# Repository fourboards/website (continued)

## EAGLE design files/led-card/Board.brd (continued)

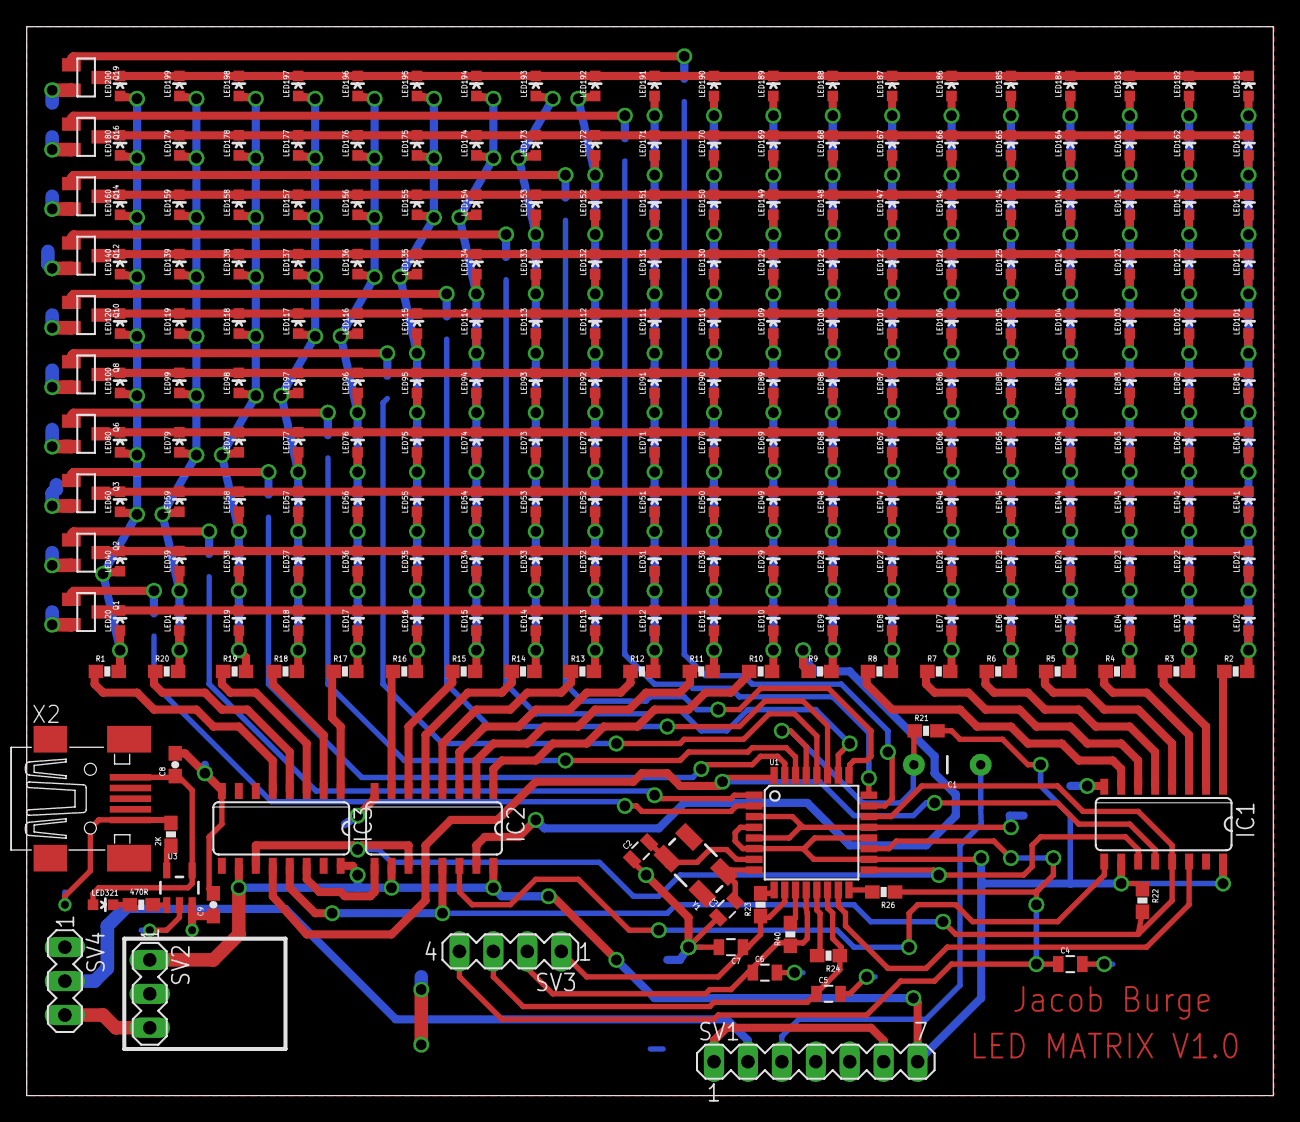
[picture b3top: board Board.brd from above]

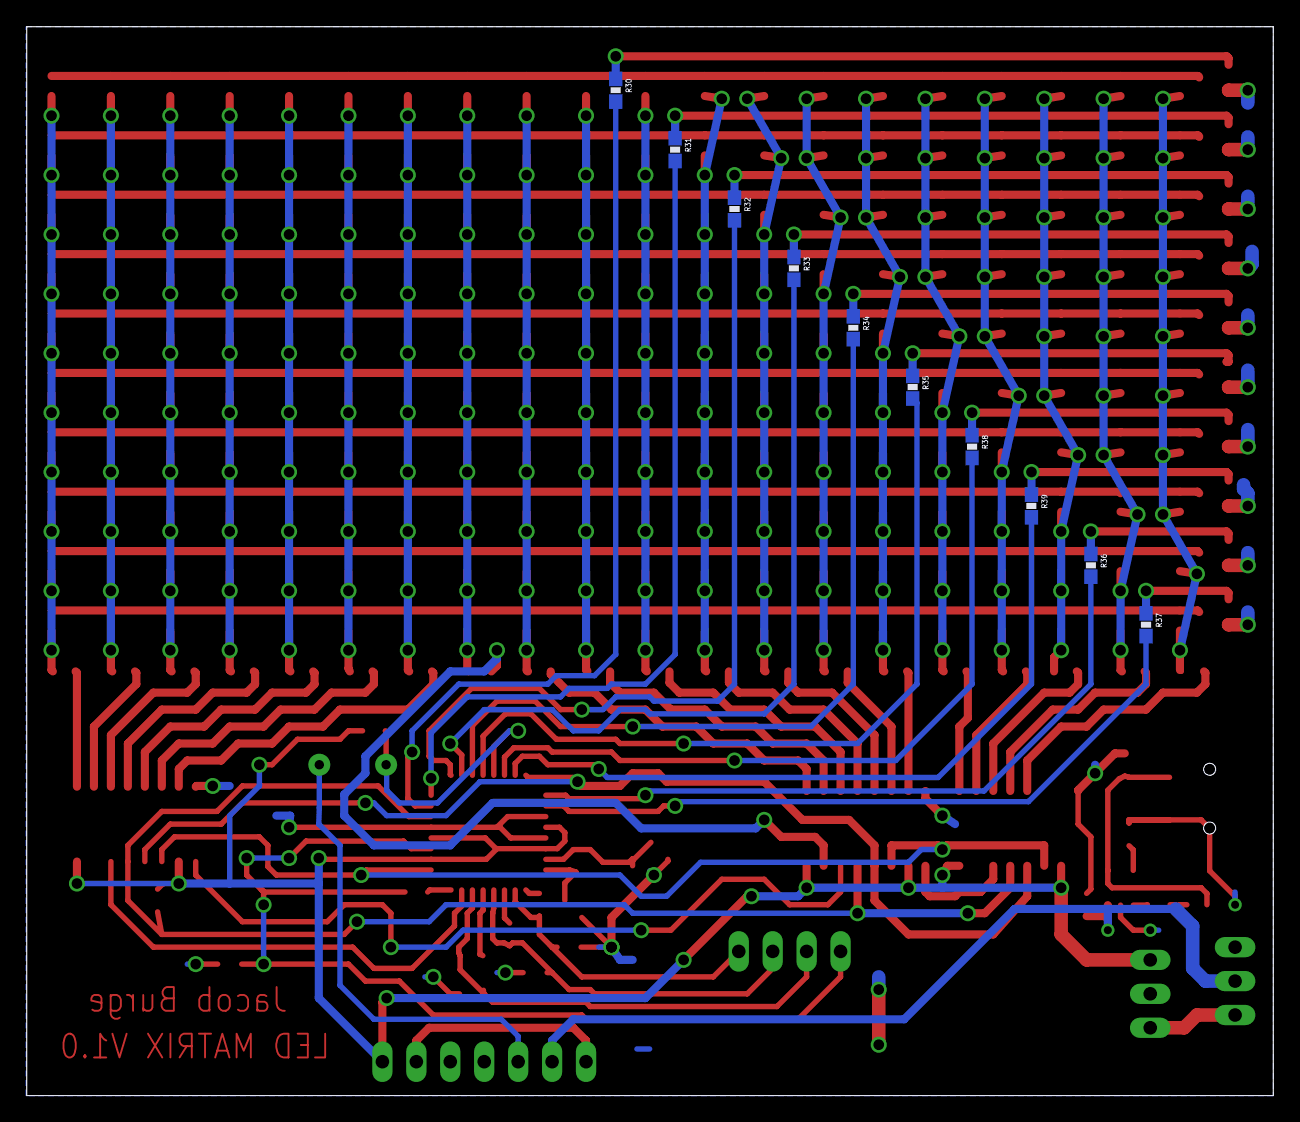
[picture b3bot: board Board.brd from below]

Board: 2 copper layers, 93.3 x 80.0 mm, 269 parts (10 on the bottom side), 96 nets.

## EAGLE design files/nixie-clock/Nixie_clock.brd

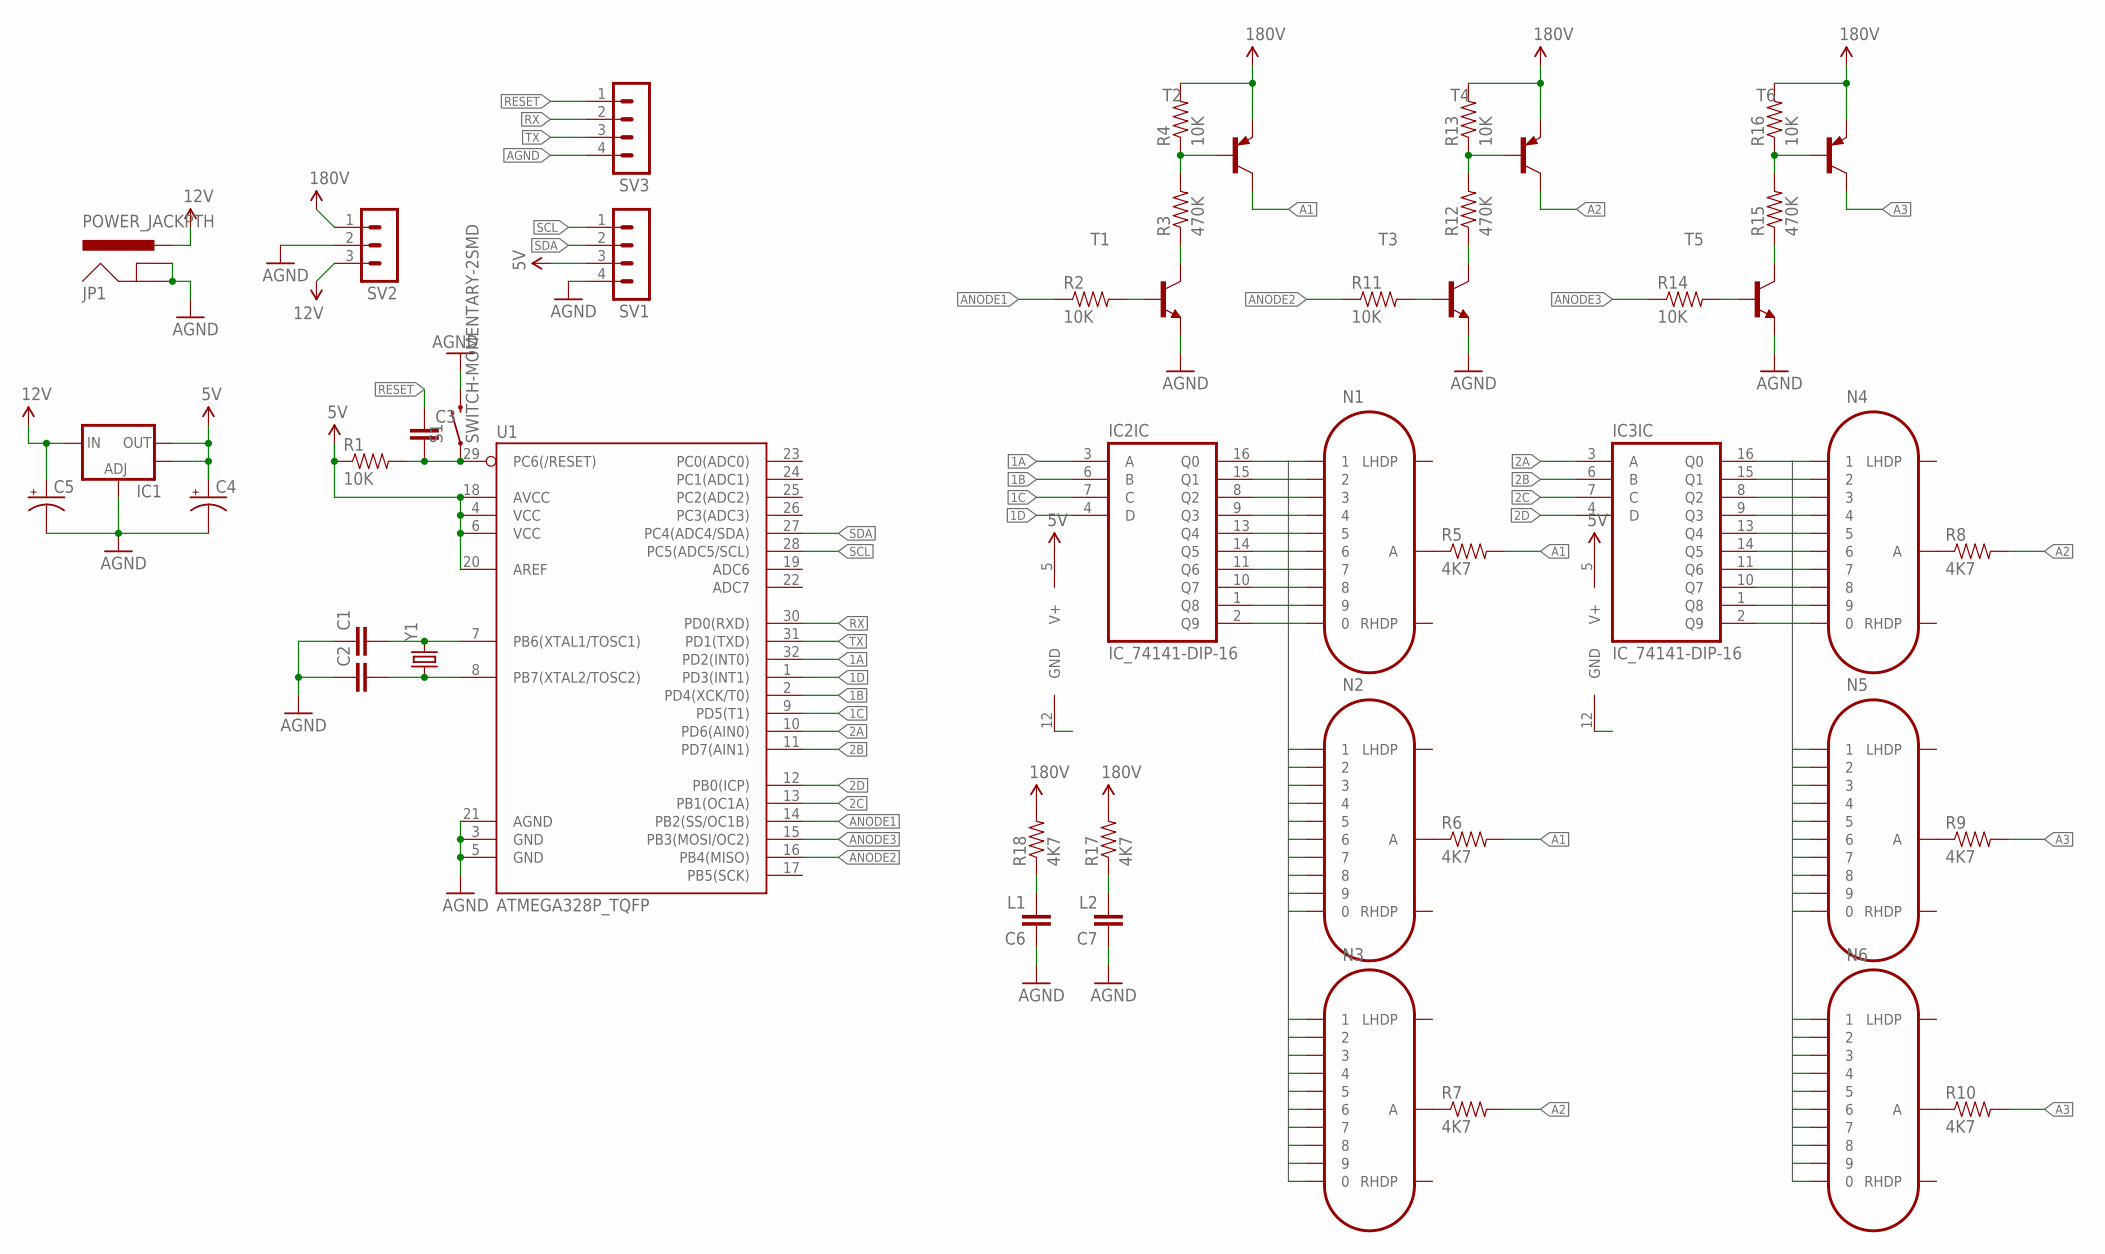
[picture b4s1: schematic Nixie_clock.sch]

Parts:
C1, C2, C3: CAPPTH; CAP-PTH-SMALL
C4, C5: 10UF-25V-20%(PTH); CPOL-RADIAL-10UF-25V
C6: L1; CAP-PTH-SMALL
C7: L2; CAP-PTH-SMALL
IC1: V_REG_LM1117SOT223; SOT223
IC2, IC3: IC_74141-DIP-16; DIL16
JP1: POWER_JACKPTH; POWER_JACK_PTH
N1, N2, N3, N4, N5, N6: IN-14
R1, R2, R11, R14: 10K; 0603-RES
R3, R12, R15: 470K; AXIAL-0.3
R4, R13, R16: 10K; AXIAL-0.3
R5, R6, R7, R8, R9, R10, R17, R18: 4K7; AXIAL-0.3
S1: SWITCH-MOMENTARY-2SMD; TACTILE-SWITCH-SMD
SV1, SV3: MA04-1
SV2: MA03-1
T1, T3, T5: MPSA42-NPN-TO92-EBC; TO92-EBC
T2, T4, T6: MPSA92-PNP-TO92-EBC; TO92-EBC
U1: ATMEGA328P_TQFP; TQFP32-08
Y1: CRYSTALHC49US; HC49US

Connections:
1.0V: R4.P$2 (2), R13.P$2 (2), R16.P$2 (2), R17.P$2 (2), R18.P$2 (2), SV2.1, T2.E, T4.E, T6.E
1A: IC2.3 (A), U1.32 (PD2(INT0))
1B: IC2.6 (B), U1.2 (PD4(XCK/T0))
1C: IC2.7 (C), U1.9 (PD5(T1))
1D: IC2.4 (D), U1.1 (PD3(INT1))
2A: IC3.3 (A), U1.10 (PD6(AIN0))
2B: IC3.6 (B), U1.11 (PD7(AIN1))
2C: IC3.7 (C), U1.13 (PB1(OC1A))
2D: IC3.4 (D), U1.12 (PB0(ICP))
5V: C4.1 (+), IC1.2 (OUT), IC1.4 (OUT), IC2.5 (V+), IC3.5 (V+), R1.1, SV1.3, U1.4 (VCC), U1.6 (VCC), U1.18 (AVCC), U1.20 (AREF)
12V: C5.1 (+), IC1.3 (IN), JP1.PWR, SV2.3
A1: R5.P$2 (2), R6.P$2 (2), T2.C
A2: R7.P$2 (2), R8.P$2 (2), T4.C
A3: R9.P$2 (2), R10.P$2 (2), T6.C
AGND: C1.1, C2.1, C4.2 (-), C5.2 (-), C6.1, C7.1, IC1.1 (ADJ), IC2.12 (GND), IC3.12 (GND), JP1.GND, JP1.GNDBREAK, S1.3 (2), SV1.4, SV2.2, SV3.4, T1.E, T3.E, T5.E, U1.3 (GND), U1.5 (GND), U1.21 (AGND)
ANODE1: R2.1, U1.14 (PB2(SS/OC1B))
ANODE2: R11.1, U1.16 (PB4(MISO))
ANODE3: R14.1, U1.15 (PB3(MOSI/OC2))
unnamed: C1.2, U1.7 (PB6(XTAL1/TOSC1)), Y1.2
unnamed: C2.2, U1.8 (PB7(XTAL2/TOSC2)), Y1.1
unnamed: C3.2, R1.2, S1.1, U1.29 (PC6(/RESET))
unnamed: R2.2, T1.B
unnamed: R3.P$1 (1), T1.C
unnamed: R3.P$2 (2), R4.P$1 (1), T2.B
unnamed: N1.A, R5.P$1 (1)
unnamed: N2.A, R6.P$1 (1)
unnamed: N3.A, R7.P$1 (1)
unnamed: N4.A, R8.P$1 (1)
unnamed: N5.A, R9.P$1 (1)
unnamed: N6.A, R10.P$1 (1)
unnamed: R11.2, T3.B
unnamed: R12.P$1 (1), T3.C
unnamed: R12.P$2 (2), R13.P$1 (1), T4.B
unnamed: R14.2, T5.B
unnamed: R15.P$1 (1), T5.C
unnamed: R15.P$2 (2), R16.P$1 (1), T6.B
unnamed: C6.2, R18.P$1 (1)
unnamed: C7.2, R17.P$1 (1)
NIXIE0: IC2.16 (Q0), N1.0, N2.0, N3.0
NIXIE1: IC2.15 (Q1), N1.1, N2.1, N3.1
NIXIE2: IC2.8 (Q2), N1.2, N2.2, N3.2
NIXIE3: IC2.9 (Q3), N1.3, N2.3, N3.3
NIXIE4: IC2.13 (Q4), N1.4, N2.4, N3.4
NIXIE5: IC2.14 (Q5), N1.5, N2.5, N3.5
NIXIE6: IC2.11 (Q6), N1.6, N2.6, N3.6
NIXIE7: IC2.10 (Q7), N1.7, N2.7, N3.7
NIXIE8: IC2.1 (Q8), N1.8, N2.8, N3.8
NIXIE9: IC2.2 (Q9), N1.9, N2.9, N3.9
NIXIEB0: IC3.16 (Q0), N4.0, N5.0, N6.0
NIXIEB1: IC3.15 (Q1), N4.1, N5.1, N6.1
NIXIEB2: IC3.8 (Q2), N4.2, N5.2, N6.2
NIXIEB3: IC3.9 (Q3), N4.3, N5.3, N6.3
NIXIEB4: IC3.13 (Q4), N4.4, N5.4, N6.4
NIXIEB5: IC3.14 (Q5), N4.5, N5.5, N6.5
NIXIEB6: IC3.11 (Q6), N4.6, N5.6, N6.6
NIXIEB7: IC3.10 (Q7), N4.7, N5.7, N6.7
NIXIEB8: IC3.1 (Q8), N4.8, N5.8, N6.8
NIXIEB9: IC3.2 (Q9), N4.9, N5.9, N6.9
RESET: C3.1, SV3.1
RX: SV3.2, U1.30 (PD0(RXD))
SCL: SV1.1, U1.28 (PC5(ADC5/SCL))
SDA: SV1.2, U1.27 (PC4(ADC4/SDA))
TX: SV3.3, U1.31 (PD1(TXD))

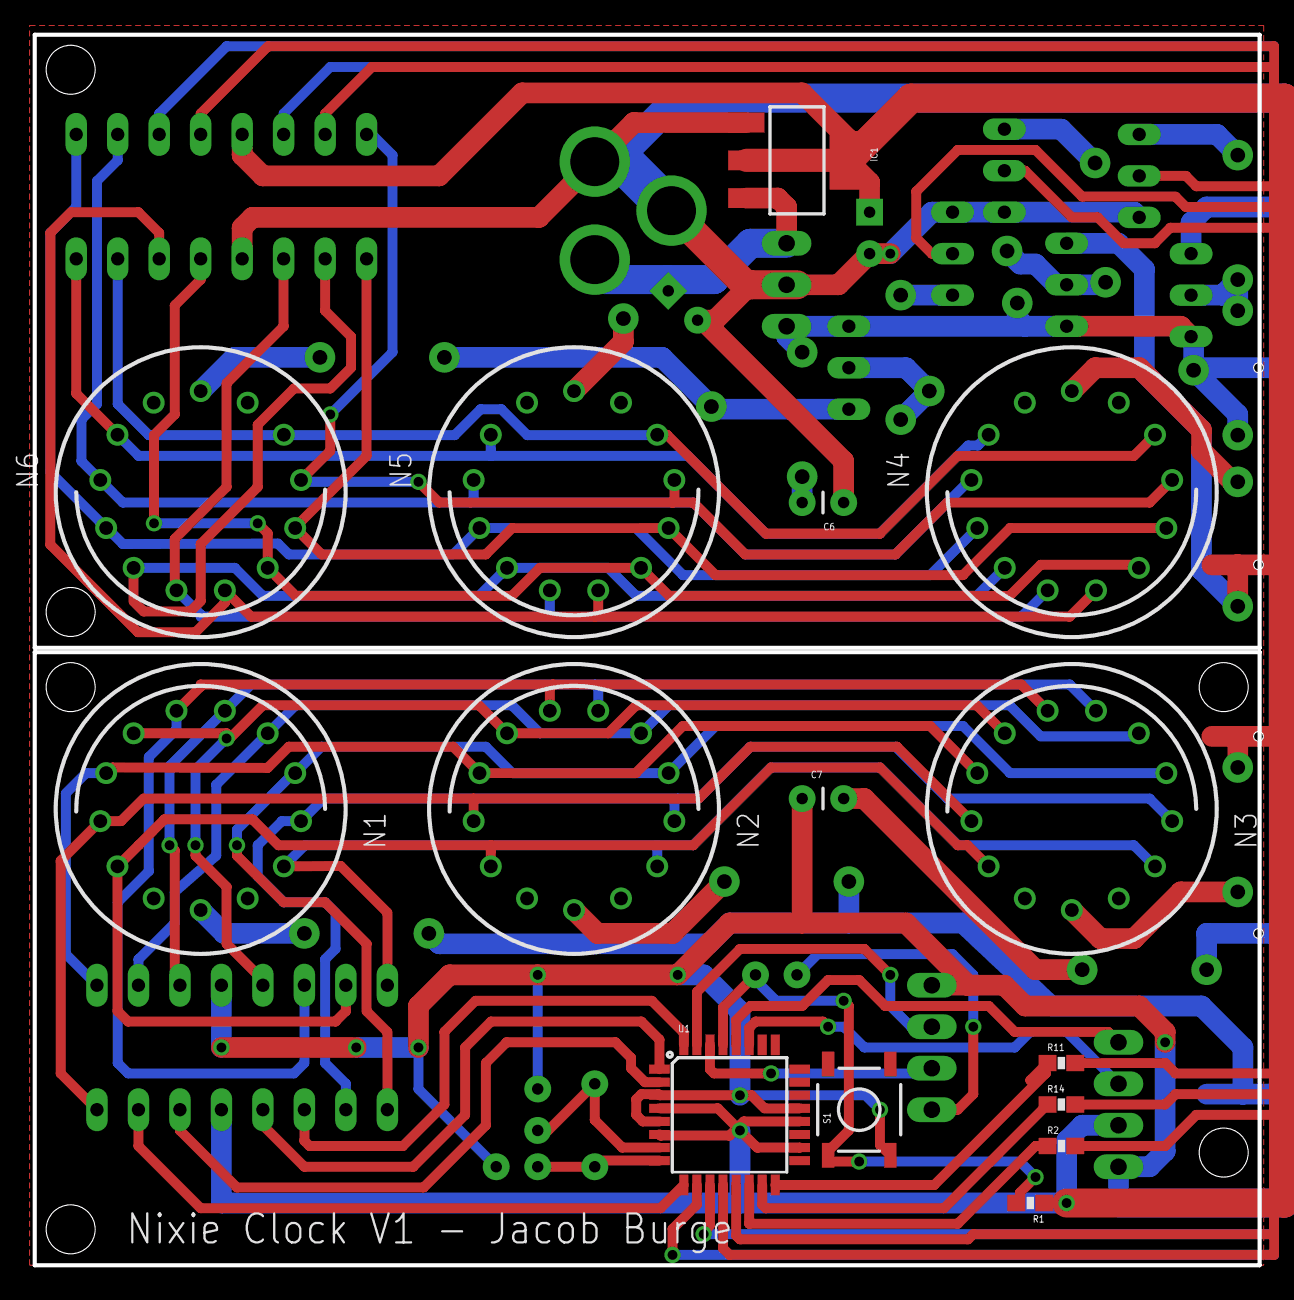
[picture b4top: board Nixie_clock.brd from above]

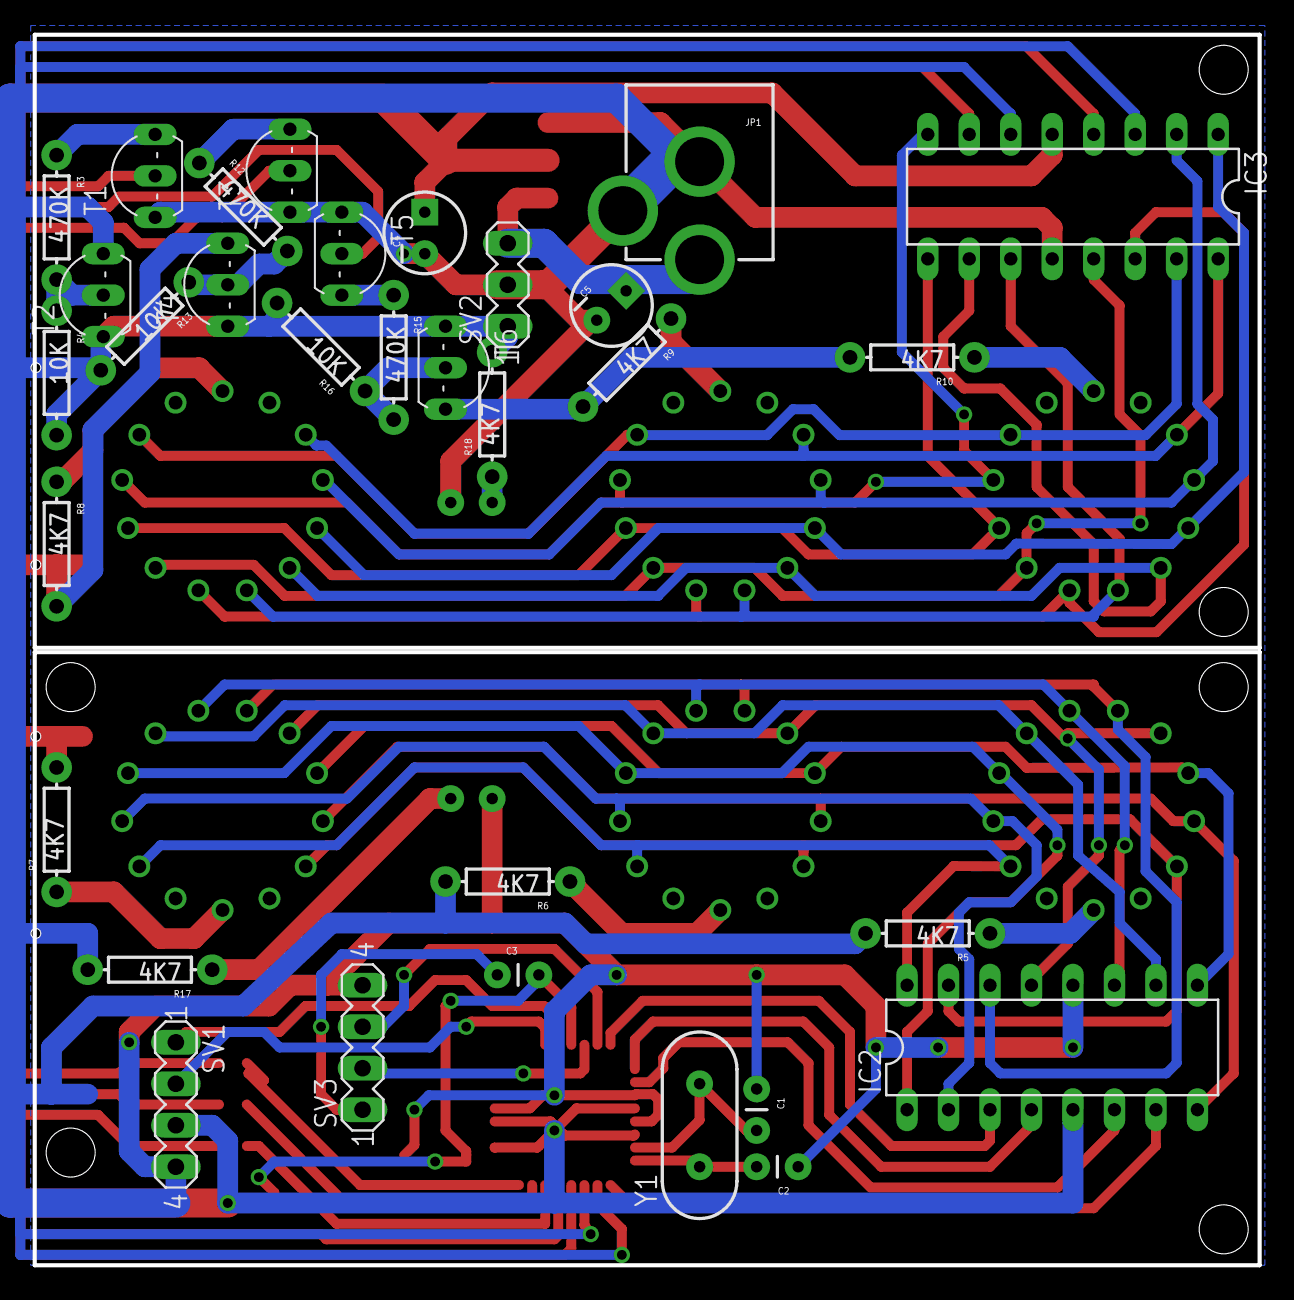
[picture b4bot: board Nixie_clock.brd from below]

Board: 2 copper layers, 75.0 x 75.3 mm, 47 parts (32 on the bottom side), 63 nets.

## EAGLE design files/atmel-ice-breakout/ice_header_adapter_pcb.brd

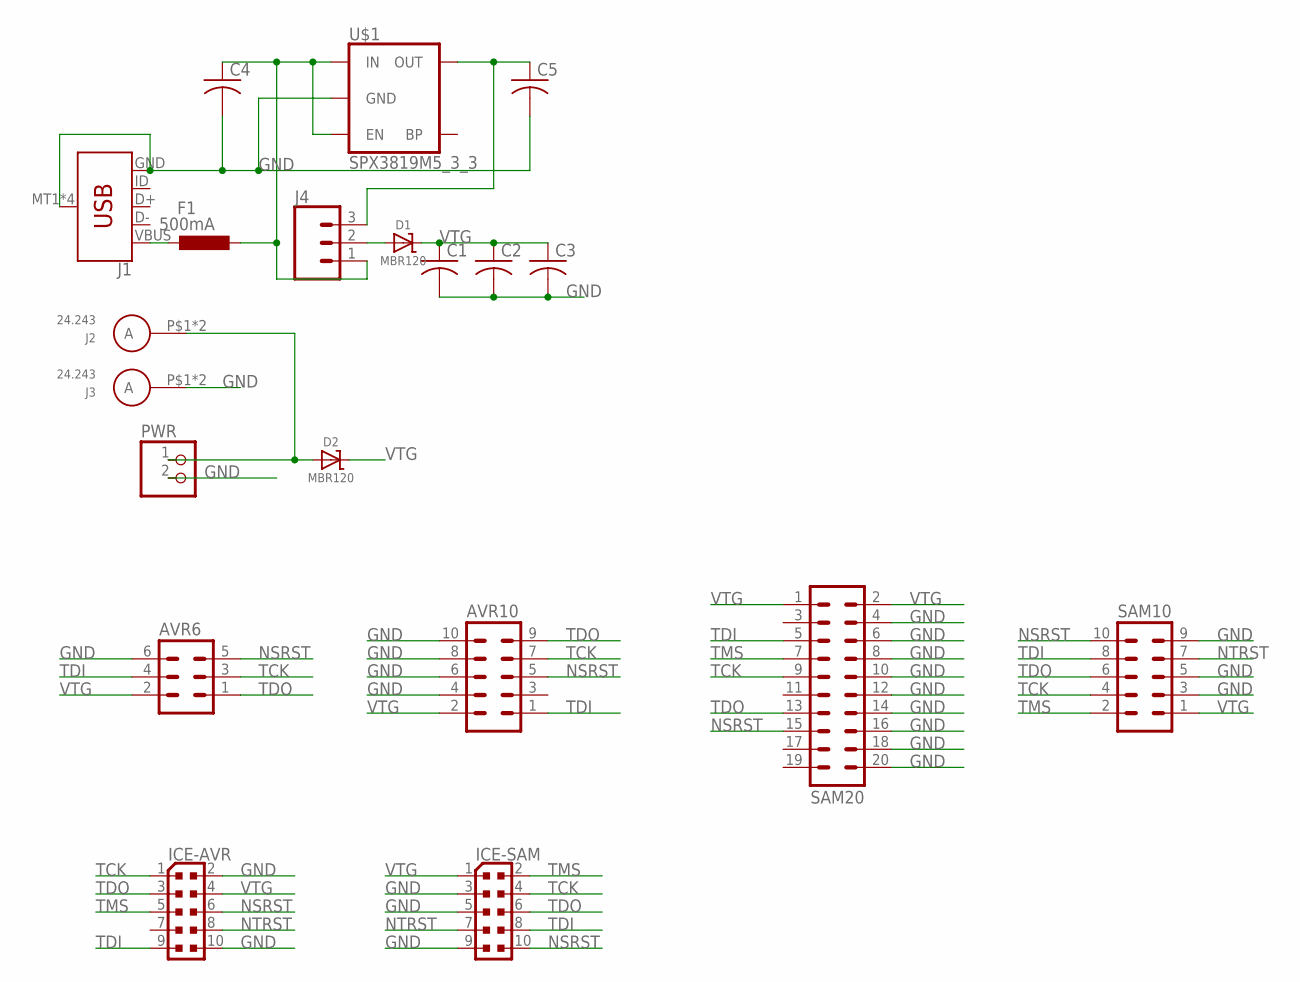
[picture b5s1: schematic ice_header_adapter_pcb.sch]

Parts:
AVR6: ML6
AVR10: ML10
C1, C2, C3, C4, C5: C-USC0603; C0603
D1, D2: MBR120; SOD-123
F1: 500mA; L1812
ICE-AVR: PINHEAD_PINHD-2X5PASSO127; PINHEAD_2X05_127
ICE-SAM: PINHEAD_PINHD-2X5PASSO127; PINHEAD_2X05_127
J1: USB_MICRO-B_SMT; USB-MICROB
J2, J3: 24.243
J4: CONN_03LOCK; 1X03_LOCK
PWR: PINHD-1X2/90; 1X02/90
SAM10: ML10
SAM20: ML20
U$1: SPX3819M5_3_3; SOT23-5

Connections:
GND: AVR6.6, AVR10.4, AVR10.6, AVR10.8, AVR10.10, C1.2, C2.2, C3.2, C4.2, C5.2, ICE-AVR.2, ICE-AVR.10, ICE-SAM.3, ICE-SAM.5, ICE-SAM.9, J1.GND, J1.MT1 (SHIELD), J1.MT2 (SHIELD), J1.P$1 (SHIELD), J1.P$2 (SHIELD), J3.P$1, J3.P$2, PWR.2, SAM10.3, SAM10.5, SAM10.9, SAM20.4, SAM20.6, SAM20.8, SAM20.10, SAM20.12, SAM20.14, SAM20.16, SAM20.18, SAM20.20, U$1.2 (GND)
unnamed: D2.A, J2.P$1, J2.P$2, PWR.1
unnamed: C4.1, F1.1, J4.1, U$1.1 (IN), U$1.3 (EN)
unnamed: D1.A, J4.2
unnamed: F1.2, J1.VBUS
unnamed: C5.1, J4.3, U$1.5 (OUT)
NSRST: AVR6.5, AVR10.5, ICE-AVR.6, ICE-SAM.10, SAM10.10, SAM20.15
NTRST: ICE-AVR.8, ICE-SAM.7, SAM10.7
TCK: AVR6.3, AVR10.7, ICE-AVR.1, ICE-SAM.4, SAM10.4, SAM20.9
TDI: AVR6.4, AVR10.1, ICE-AVR.9, ICE-SAM.8, SAM10.8, SAM20.5
TDO: AVR6.1, AVR10.9, ICE-AVR.3, ICE-SAM.6, SAM10.6, SAM20.13
TMS: ICE-AVR.5, ICE-SAM.2, SAM10.2, SAM20.7
VTG: AVR6.2, AVR10.2, C1.1, C2.1, C3.1, D1.C, D2.C, ICE-AVR.4, ICE-SAM.1, SAM10.1, SAM20.1, SAM20.2

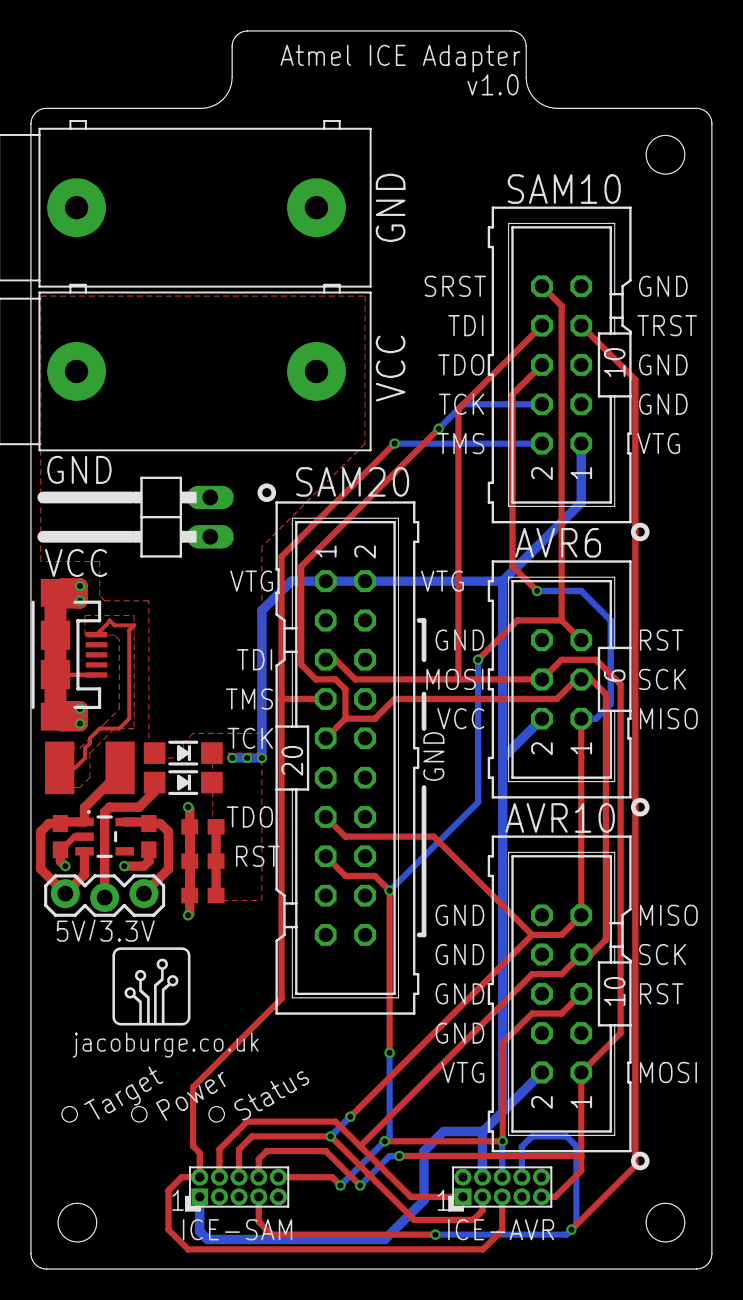
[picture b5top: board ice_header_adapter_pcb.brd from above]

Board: 2 copper layers, 44.0 x 80.0 mm, 20 parts (0 on the bottom side), 13 nets.

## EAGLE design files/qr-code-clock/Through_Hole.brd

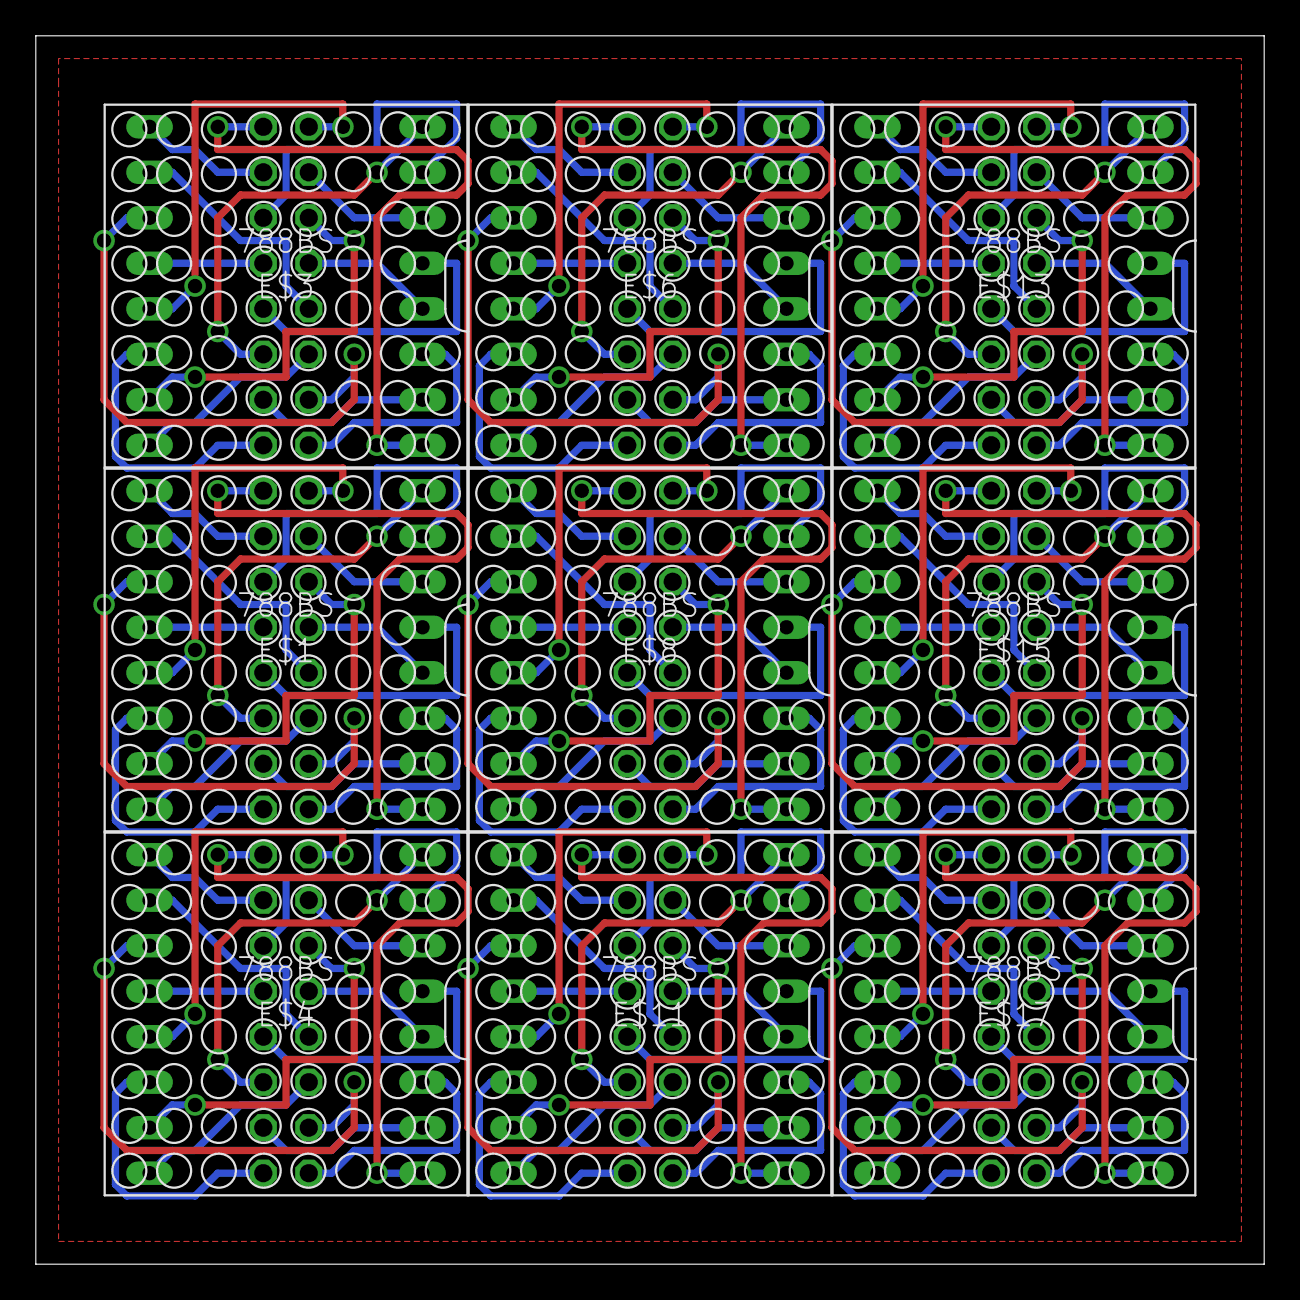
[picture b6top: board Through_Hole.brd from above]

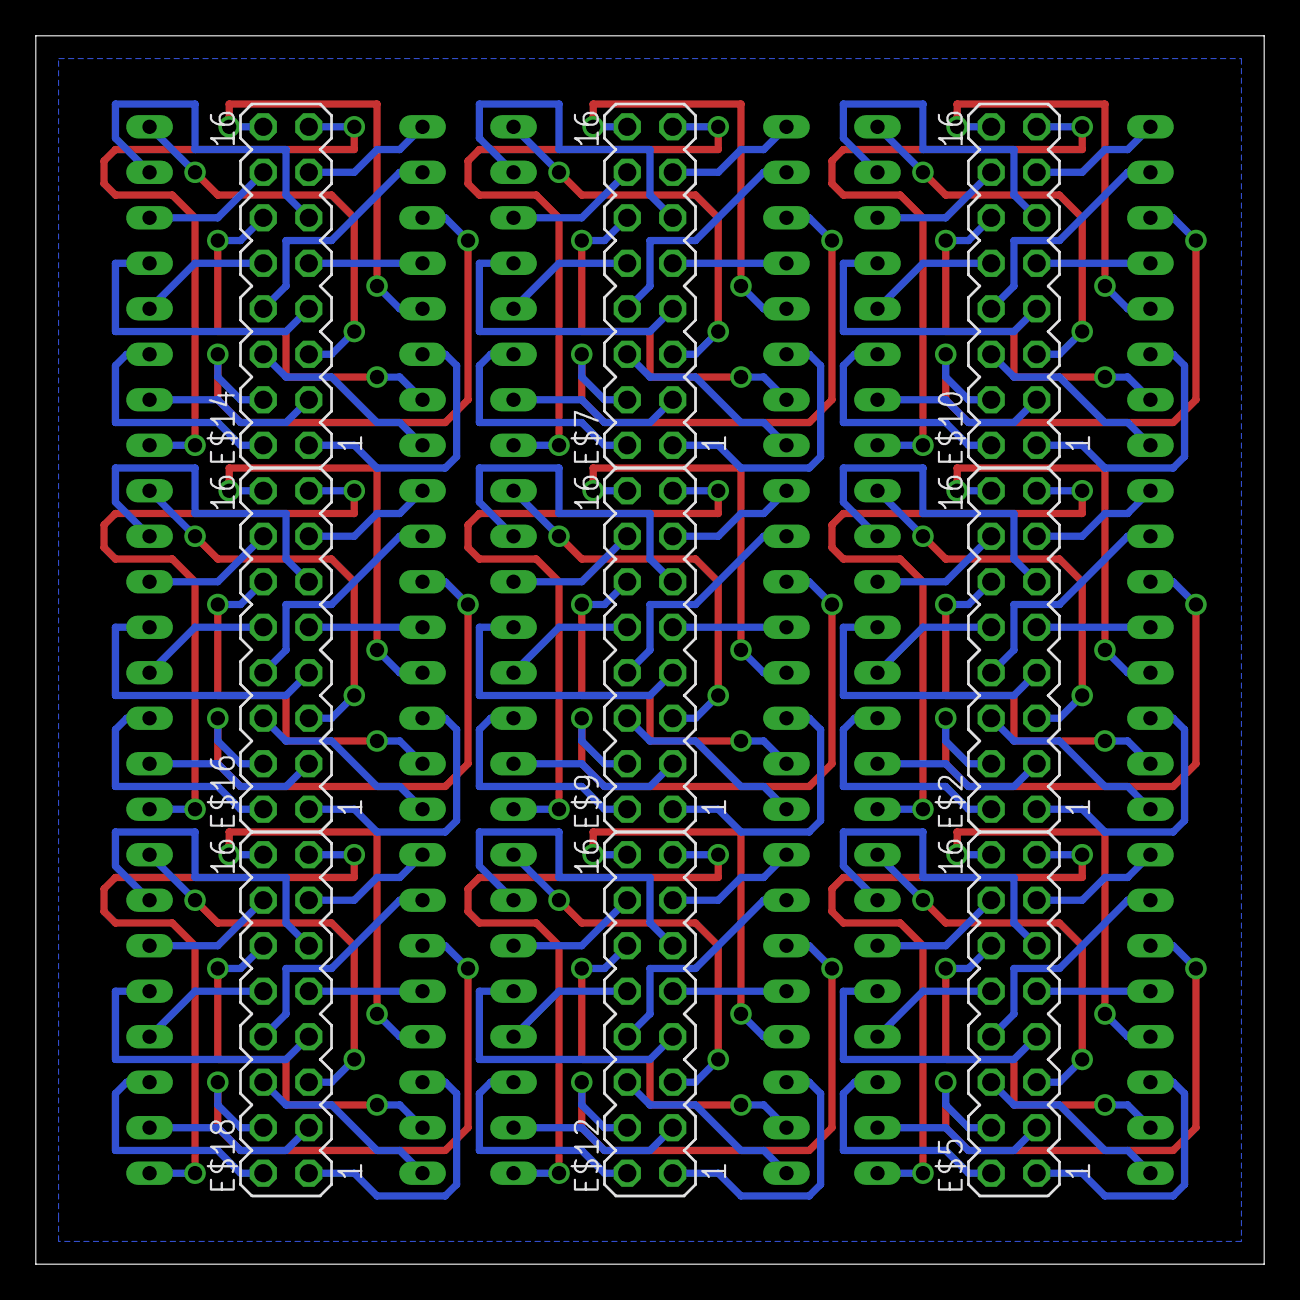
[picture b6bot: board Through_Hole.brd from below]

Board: 2 copper layers, 68.6 x 68.6 mm, 18 parts (9 on the bottom side), 144 nets.

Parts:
E$1, E$3, E$4, E$6, E$8, E$11, E$13, E$15, E$17: 788BS_DOT_MATRIX
E$2, E$5, E$7, E$9, E$10, E$12, E$14, E$16, E$18: MA08-2

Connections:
S$1: E$3.ROW1, E$10.13
S$2: E$3.ROW2, E$10.1
S$3: E$3.ROW3, E$10.5
S$4: E$3.ROW4, E$10.9
S$5: E$3.ROW5, E$10.15
S$6: E$3.ROW6, E$10.11
S$7: E$3.ROW7, E$10.3
S$8: E$3.ROW8, E$10.7
S$9: E$3.COL1, E$10.16
S$10: E$3.COL2, E$10.2
S$11: E$3.COL3, E$10.10
S$12: E$3.COL4, E$10.8
S$13: E$3.COL5, E$10.14
S$14: E$3.COL6, E$10.4
S$15: E$3.COL7, E$10.12
S$16: E$3.COL8, E$10.6
S$17: E$1.ROW2, E$2.1
S$18: E$1.ROW1, E$2.13
S$19: E$1.ROW3, E$2.5
S$20: E$1.ROW4, E$2.9
S$21: E$1.ROW5, E$2.15
S$22: E$1.ROW6, E$2.11
S$23: E$1.ROW7, E$2.3
S$24: E$1.ROW8, E$2.7
S$25: E$1.COL1, E$2.16
S$26: E$1.COL2, E$2.2
S$27: E$1.COL4, E$2.8
S$28: E$1.COL5, E$2.14
S$29: E$1.COL6, E$2.4
S$30: E$1.COL3, E$2.10
S$31: E$1.COL7, E$2.12
S$32: E$1.COL8, E$2.6
S$33: E$4.ROW2, E$5.1
S$34: E$4.ROW1, E$5.13
S$35: E$4.ROW3, E$5.5
S$36: E$4.ROW4, E$5.9
S$37: E$4.ROW5, E$5.15
S$38: E$4.ROW6, E$5.11
S$39: E$4.ROW7, E$5.3
S$40: E$4.ROW8, E$5.7
S$41: E$4.COL1, E$5.16
S$42: E$4.COL2, E$5.2
S$43: E$4.COL4, E$5.8
S$44: E$4.COL5, E$5.14
S$45: E$4.COL6, E$5.4
S$46: E$4.COL3, E$5.10
S$47: E$4.COL7, E$5.12
S$48: E$4.COL8, E$5.6
S$49: E$6.ROW2, E$7.1
S$50: E$6.ROW1, E$7.13
S$51: E$6.ROW3, E$7.5
S$52: E$6.ROW4, E$7.9
S$53: E$6.ROW5, E$7.15
S$54: E$6.ROW6, E$7.11
S$55: E$6.ROW7, E$7.3
S$56: E$6.ROW8, E$7.7
S$57: E$6.COL1, E$7.16
S$58: E$6.COL2, E$7.2
S$59: E$6.COL4, E$7.8
S$60: E$6.COL5, E$7.14
S$61: E$6.COL6, E$7.4
S$62: E$6.COL3, E$7.10
S$63: E$6.COL7, E$7.12
S$64: E$6.COL8, E$7.6
S$65: E$8.ROW2, E$9.1
S$66: E$8.ROW1, E$9.13
S$67: E$8.ROW3, E$9.5
S$68: E$8.ROW4, E$9.9
S$69: E$8.ROW5, E$9.15
S$70: E$8.ROW6, E$9.11
S$71: E$8.ROW7, E$9.3
S$72: E$8.ROW8, E$9.7
S$73: E$8.COL1, E$9.16
S$74: E$8.COL2, E$9.2
S$75: E$8.COL4, E$9.8
S$76: E$8.COL5, E$9.14
S$77: E$8.COL6, E$9.4
S$78: E$8.COL3, E$9.10
S$79: E$8.COL7, E$9.12
S$80: E$8.COL8, E$9.6
S$81: E$11.ROW2, E$12.1
S$82: E$11.ROW1, E$12.13
S$83: E$11.ROW3, E$12.5
S$84: E$11.ROW4, E$12.9
S$85: E$11.ROW5, E$12.15
S$86: E$11.ROW6, E$12.11
S$87: E$11.ROW7, E$12.3
S$88: E$11.ROW8, E$12.7
S$89: E$11.COL1, E$12.16
S$90: E$11.COL2, E$12.2
S$91: E$11.COL4, E$12.8
S$92: E$11.COL5, E$12.14
S$93: E$11.COL6, E$12.4
S$94: E$11.COL3, E$12.10
S$95: E$11.COL7, E$12.12
S$96: E$11.COL8, E$12.6
S$97: E$13.ROW2, E$14.1
S$98: E$13.ROW1, E$14.13
S$99: E$13.ROW3, E$14.5
S$100: E$13.ROW4, E$14.9
S$101: E$13.ROW5, E$14.15
S$102: E$13.ROW6, E$14.11
S$103: E$13.ROW7, E$14.3
S$104: E$13.ROW8, E$14.7
S$105: E$13.COL1, E$14.16
S$106: E$13.COL2, E$14.2
S$107: E$13.COL4, E$14.8
S$108: E$13.COL5, E$14.14
S$109: E$13.COL6, E$14.4
S$110: E$13.COL3, E$14.10
S$111: E$13.COL7, E$14.12
S$112: E$13.COL8, E$14.6
S$113: E$15.ROW2, E$16.1
S$114: E$15.ROW1, E$16.13
S$115: E$15.ROW3, E$16.5
S$116: E$15.ROW4, E$16.9
S$117: E$15.ROW5, E$16.15
S$118: E$15.ROW6, E$16.11
S$119: E$15.ROW7, E$16.3
S$120: E$15.ROW8, E$16.7
S$121: E$15.COL1, E$16.16
S$122: E$15.COL2, E$16.2
S$123: E$15.COL4, E$16.8
S$124: E$15.COL5, E$16.14
S$125: E$15.COL6, E$16.4
S$126: E$15.COL3, E$16.10
S$127: E$15.COL7, E$16.12
S$128: E$15.COL8, E$16.6
S$129: E$17.ROW2, E$18.1
S$130: E$17.ROW1, E$18.13
S$131: E$17.ROW3, E$18.5
S$132: E$17.ROW4, E$18.9
S$133: E$17.ROW5, E$18.15
S$134: E$17.ROW6, E$18.11
S$135: E$17.ROW7, E$18.3
S$136: E$17.ROW8, E$18.7
S$137: E$17.COL1, E$18.16
S$138: E$17.COL2, E$18.2
S$139: E$17.COL4, E$18.8
S$140: E$17.COL5, E$18.14
S$141: E$17.COL6, E$18.4
S$142: E$17.COL3, E$18.10
S$143: E$17.COL7, E$18.12
S$144: E$17.COL8, E$18.6
